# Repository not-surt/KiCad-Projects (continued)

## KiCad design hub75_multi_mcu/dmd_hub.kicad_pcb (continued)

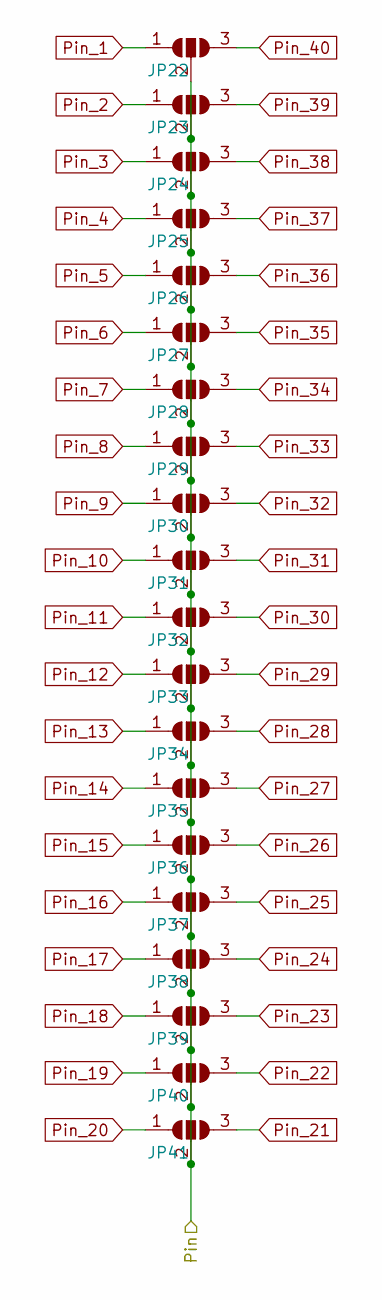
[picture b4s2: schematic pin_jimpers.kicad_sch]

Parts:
JP22, JP23, JP24, JP25, JP26, JP27, JP28, JP29, JP30, JP31, JP32, JP33, JP34, JP35, JP36, JP37, JP38, JP39, JP40, JP41: SolderJumper_3_Open; SolderJumper-mini-3

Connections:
Pin_1: JP22.1 (A); also elsewhere on the board
Pin_2: JP23.1 (A); also elsewhere on the board
Pin_3: JP24.1 (A); also elsewhere on the board
Pin_4: JP25.1 (A); also elsewhere on the board
Pin_5: JP26.1 (A); also elsewhere on the board
Pin_6: JP27.1 (A); also elsewhere on the board
Pin_7: JP28.1 (A); also elsewhere on the board
Pin_8: JP29.1 (A); also elsewhere on the board
Pin_9: JP30.1 (A); also elsewhere on the board
Pin_10: JP31.1 (A); also elsewhere on the board
Pin_11: JP32.1 (A); also elsewhere on the board
Pin_12: JP33.1 (A); also elsewhere on the board
Pin_13: JP34.1 (A); also elsewhere on the board
Pin_14: JP35.1 (A); also elsewhere on the board
Pin_15: JP36.1 (A); also elsewhere on the board
Pin_16: JP37.1 (A); also elsewhere on the board
Pin_17: JP38.1 (A); also elsewhere on the board
Pin_18: JP39.1 (A); also elsewhere on the board
Pin_19: JP40.1 (A); also elsewhere on the board
Pin_20: JP41.1 (A); also elsewhere on the board
Pin_21: JP41.3 (B); also elsewhere on the board
Pin_22: JP40.3 (B); also elsewhere on the board
Pin_23: JP39.3 (B); also elsewhere on the board
Pin_24: JP38.3 (B); also elsewhere on the board
Pin_25: JP37.3 (B); also elsewhere on the board
Pin_26: JP36.3 (B); also elsewhere on the board
Pin_27: JP35.3 (B); also elsewhere on the board
Pin_28: JP34.3 (B); also elsewhere on the board
Pin_29: JP33.3 (B); also elsewhere on the board
Pin_30: JP32.3 (B); also elsewhere on the board
Pin_31: JP31.3 (B); also elsewhere on the board
Pin_32: JP30.3 (B); also elsewhere on the board
Pin_33: JP29.3 (B); also elsewhere on the board
Pin_34: JP28.3 (B); also elsewhere on the board
Pin_35: JP27.3 (B); also elsewhere on the board
Pin_36: JP26.3 (B); also elsewhere on the board
Pin_37: JP25.3 (B); also elsewhere on the board
Pin_38: JP24.3 (B); also elsewhere on the board
Pin_39: JP23.3 (B); also elsewhere on the board
Pin_40: JP22.3 (B); also elsewhere on the board
VCC: JP22.2 (C), JP23.2 (C), JP24.2 (C), JP25.2 (C), JP26.2 (C), JP27.2 (C), JP28.2 (C), JP29.2 (C), JP30.2 (C), JP31.2 (C), JP32.2 (C), JP33.2 (C), JP34.2 (C), JP35.2 (C), JP36.2 (C), JP37.2 (C), JP38.2 (C), JP39.2 (C), JP40.2 (C), JP41.2 (C); also elsewhere on the board

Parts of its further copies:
JP2, JP3, JP4, JP5, JP6, JP7, JP8, JP9, JP10, JP11, JP12, JP13, JP14, JP15, JP16, JP17, JP18, JP19, JP20, JP21, JP42, JP43, JP44, JP45, JP46, JP47, JP48, JP49, JP50, JP51, JP52, JP53, JP54, JP55, JP56, JP57, JP58, JP59, JP60, JP61, JP62, JP63, JP64, JP65, JP66, JP67, JP68, JP69, JP70, JP71, JP72, JP73, JP74, JP75, JP76, JP77, JP78, JP79, JP80, JP81, JP82, JP83, JP84, JP85, JP86, JP87, JP88, JP89, JP90, JP91, JP92, JP93, JP94, JP95, JP96, JP97, JP98, JP99, JP100, JP101, JP102, JP103, JP104, JP105, JP106, JP107, JP108, JP109, JP110, JP111, JP112, JP113, JP114, JP115, JP116, JP117, JP118, JP119, JP120, JP121, JP122, JP123, JP124, JP125, JP126, JP127, JP128, JP129, JP130, JP131, JP132, JP133, JP134, JP135, JP136, JP137, JP138, JP139, JP140, JP141, JP142, JP143, JP144, JP145, JP146, JP147, JP148, JP149, JP150, JP151, JP152, JP153, JP154, JP155, JP156, JP157, JP158, JP159, JP160, JP161, JP162, JP163, JP164, JP165, JP166, JP167, JP168, JP169, JP170, JP171, JP172, JP173, JP174, JP175, JP176, JP177, JP178, JP179, JP180, JP181, JP182, JP183, JP184, JP185, JP186, JP187, JP188, JP189, JP190, JP191, JP192, JP193, JP194, JP195, JP196, JP197, JP198, JP199, JP200, JP201, JP202, JP203, JP204, JP205, JP206, JP207, JP208, JP209, JP210, JP211, JP212, JP213, JP214, JP215, JP216, JP217, JP218, JP219, JP220, JP221, JP222, JP223, JP224, JP225, JP226, JP227, JP228, JP229, JP230, JP231, JP232, JP233, JP234, JP235, JP236, JP237, JP238, JP239, JP240, JP241, JP242, JP243, JP244, JP245, JP246, JP247, JP248, JP249, JP250, JP251, JP252, JP253, JP254, JP255, JP256, JP257, JP258, JP259, JP260, JP261, JP262, JP263, JP264, JP265, JP266, JP267, JP268, JP269, JP270, JP271, JP272, JP273, JP274, JP275, JP276, JP277, JP278, JP279, JP280, JP281, JP282, JP283, JP284, JP285, JP286, JP287, JP288, JP289, JP290, JP291, JP292, JP293, JP294, JP295, JP296, JP297, JP298, JP299, JP300, JP301, JP302, JP303, JP304, JP305, JP306, JP307, JP308, JP309, JP310, JP311, JP312, JP313, JP314, JP315, JP316, JP317, JP318, JP319, JP320, JP321: SolderJumper_3_Open; SolderJumper-mini-3

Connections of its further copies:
/IDC01 (R1): JP42.2 (C), JP43.2 (C), JP44.2 (C), JP45.2 (C), JP46.2 (C), JP47.2 (C), JP48.2 (C), JP49.2 (C), JP50.2 (C), JP51.2 (C), JP52.2 (C), JP53.2 (C), JP54.2 (C), JP55.2 (C), JP56.2 (C), JP57.2 (C), JP58.2 (C), JP59.2 (C), JP60.2 (C), JP61.2 (C); also elsewhere on the board
/IDC02 (G1): JP62.2 (C), JP63.2 (C), JP64.2 (C), JP65.2 (C), JP66.2 (C), JP67.2 (C), JP68.2 (C), JP69.2 (C), JP70.2 (C), JP71.2 (C), JP72.2 (C), JP73.2 (C), JP74.2 (C), JP75.2 (C), JP76.2 (C), JP77.2 (C), JP78.2 (C), JP79.2 (C), JP80.2 (C), JP81.2 (C); also elsewhere on the board
/IDC03 (B1): JP82.2 (C), JP83.2 (C), JP84.2 (C), JP85.2 (C), JP86.2 (C), JP87.2 (C), JP88.2 (C), JP89.2 (C), JP90.2 (C), JP91.2 (C), JP92.2 (C), JP93.2 (C), JP94.2 (C), JP95.2 (C), JP96.2 (C), JP97.2 (C), JP98.2 (C), JP99.2 (C), JP100.2 (C), JP101.2 (C); also elsewhere on the board
/IDC05 (R2): JP102.2 (C), JP103.2 (C), JP104.2 (C), JP105.2 (C), JP106.2 (C), JP107.2 (C), JP108.2 (C), JP109.2 (C), JP110.2 (C), JP111.2 (C), JP112.2 (C), JP113.2 (C), JP114.2 (C), JP115.2 (C), JP116.2 (C), JP117.2 (C), JP118.2 (C), JP119.2 (C), JP120.2 (C), JP121.2 (C); also elsewhere on the board
/IDC06 (G2): JP122.2 (C), JP123.2 (C), JP124.2 (C), JP125.2 (C), JP126.2 (C), JP127.2 (C), JP128.2 (C), JP129.2 (C), JP130.2 (C), JP131.2 (C), JP132.2 (C), JP133.2 (C), JP134.2 (C), JP135.2 (C), JP136.2 (C), JP137.2 (C), JP138.2 (C), JP139.2 (C), JP140.2 (C), JP141.2 (C); also elsewhere on the board
/IDC07 (B2): JP142.2 (C), JP143.2 (C), JP144.2 (C), JP145.2 (C), JP146.2 (C), JP147.2 (C), JP148.2 (C), JP149.2 (C), JP150.2 (C), JP151.2 (C), JP152.2 (C), JP153.2 (C), JP154.2 (C), JP155.2 (C), JP156.2 (C), JP157.2 (C), JP158.2 (C), JP159.2 (C), JP160.2 (C), JP161.2 (C); also elsewhere on the board
/IDC08 (E): JP162.2 (C), JP163.2 (C), JP164.2 (C), JP165.2 (C), JP166.2 (C), JP167.2 (C), JP168.2 (C), JP169.2 (C), JP170.2 (C), JP171.2 (C), JP172.2 (C), JP173.2 (C), JP174.2 (C), JP175.2 (C), JP176.2 (C), JP177.2 (C), JP178.2 (C), JP179.2 (C), JP180.2 (C), JP181.2 (C); also elsewhere on the board
/IDC09 (A): JP182.2 (C), JP183.2 (C), JP184.2 (C), JP185.2 (C), JP186.2 (C), JP187.2 (C), JP188.2 (C), JP189.2 (C), JP190.2 (C), JP191.2 (C), JP192.2 (C), JP193.2 (C), JP194.2 (C), JP195.2 (C), JP196.2 (C), JP197.2 (C), JP198.2 (C), JP199.2 (C), JP200.2 (C), JP201.2 (C); also elsewhere on the board
/IDC10 (B): JP202.2 (C), JP203.2 (C), JP204.2 (C), JP205.2 (C), JP206.2 (C), JP207.2 (C), JP208.2 (C), JP209.2 (C), JP210.2 (C), JP211.2 (C), JP212.2 (C), JP213.2 (C), JP214.2 (C), JP215.2 (C), JP216.2 (C), JP217.2 (C), JP218.2 (C), JP219.2 (C), JP220.2 (C), JP221.2 (C); also elsewhere on the board
/IDC11 (C): JP222.2 (C), JP223.2 (C), JP224.2 (C), JP225.2 (C), JP226.2 (C), JP227.2 (C), JP228.2 (C), JP229.2 (C), JP230.2 (C), JP231.2 (C), JP232.2 (C), JP233.2 (C), JP234.2 (C), JP235.2 (C), JP236.2 (C), JP237.2 (C), JP238.2 (C), JP239.2 (C), JP240.2 (C), JP241.2 (C); also elsewhere on the board
/IDC12 (D): JP242.2 (C), JP243.2 (C), JP244.2 (C), JP245.2 (C), JP246.2 (C), JP247.2 (C), JP248.2 (C), JP249.2 (C), JP250.2 (C), JP251.2 (C), JP252.2 (C), JP253.2 (C), JP254.2 (C), JP255.2 (C), JP256.2 (C), JP257.2 (C), JP258.2 (C), JP259.2 (C), JP260.2 (C), JP261.2 (C); also elsewhere on the board
/IDC13 (CLK): JP262.2 (C), JP263.2 (C), JP264.2 (C), JP265.2 (C), JP266.2 (C), JP267.2 (C), JP268.2 (C), JP269.2 (C), JP270.2 (C), JP271.2 (C), JP272.2 (C), JP273.2 (C), JP274.2 (C), JP275.2 (C), JP276.2 (C), JP277.2 (C), JP278.2 (C), JP279.2 (C), JP280.2 (C), JP281.2 (C); also elsewhere on the board
/IDC14 (LAT): JP282.2 (C), JP283.2 (C), JP284.2 (C), JP285.2 (C), JP286.2 (C), JP287.2 (C), JP288.2 (C), JP289.2 (C), JP290.2 (C), JP291.2 (C), JP292.2 (C), JP293.2 (C), JP294.2 (C), JP295.2 (C), JP296.2 (C), JP297.2 (C), JP298.2 (C), JP299.2 (C), JP300.2 (C), JP301.2 (C); also elsewhere on the board
/IDC15 (OE): JP302.2 (C), JP303.2 (C), JP304.2 (C), JP305.2 (C), JP306.2 (C), JP307.2 (C), JP308.2 (C), JP309.2 (C), JP310.2 (C), JP311.2 (C), JP312.2 (C), JP313.2 (C), JP314.2 (C), JP315.2 (C), JP316.2 (C), JP317.2 (C), JP318.2 (C), JP319.2 (C), JP320.2 (C), JP321.2 (C); also elsewhere on the board
GND: JP2.2 (C), JP3.2 (C), JP4.2 (C), JP5.2 (C), JP6.2 (C), JP7.2 (C), JP8.2 (C), JP9.2 (C), JP10.2 (C), JP11.2 (C), JP12.2 (C), JP13.2 (C), JP14.2 (C), JP15.2 (C), JP16.2 (C), JP17.2 (C), JP18.2 (C), JP19.2 (C), JP20.2 (C), JP21.2 (C); also elsewhere on the board
Pin_1: JP2.1 (A), JP42.1 (A), JP62.1 (A), JP82.1 (A), JP102.1 (A), JP122.1 (A), JP142.1 (A), JP162.1 (A), JP182.1 (A), JP202.1 (A), JP222.1 (A), JP242.1 (A), JP262.1 (A), JP282.1 (A), JP302.1 (A); also elsewhere on the board
Pin_2: JP3.1 (A), JP43.1 (A), JP63.1 (A), JP83.1 (A), JP103.1 (A), JP123.1 (A), JP143.1 (A), JP163.1 (A), JP183.1 (A), JP203.1 (A), JP223.1 (A), JP243.1 (A), JP263.1 (A), JP283.1 (A), JP303.1 (A); also elsewhere on the board
Pin_3: JP4.1 (A), JP44.1 (A), JP64.1 (A), JP84.1 (A), JP104.1 (A), JP124.1 (A), JP144.1 (A), JP164.1 (A), JP184.1 (A), JP204.1 (A), JP224.1 (A), JP244.1 (A), JP264.1 (A), JP284.1 (A), JP304.1 (A); also elsewhere on the board
Pin_4: JP5.1 (A), JP45.1 (A), JP65.1 (A), JP85.1 (A), JP105.1 (A), JP125.1 (A), JP145.1 (A), JP165.1 (A), JP185.1 (A), JP205.1 (A), JP225.1 (A), JP245.1 (A), JP265.1 (A), JP285.1 (A), JP305.1 (A); also elsewhere on the board
Pin_5: JP6.1 (A), JP46.1 (A), JP66.1 (A), JP86.1 (A), JP106.1 (A), JP126.1 (A), JP146.1 (A), JP166.1 (A), JP186.1 (A), JP206.1 (A), JP226.1 (A), JP246.1 (A), JP266.1 (A), JP286.1 (A), JP306.1 (A); also elsewhere on the board
Pin_6: JP7.1 (A), JP47.1 (A), JP67.1 (A), JP87.1 (A), JP107.1 (A), JP127.1 (A), JP147.1 (A), JP167.1 (A), JP187.1 (A), JP207.1 (A), JP227.1 (A), JP247.1 (A), JP267.1 (A), JP287.1 (A), JP307.1 (A); also elsewhere on the board
Pin_7: JP8.1 (A), JP48.1 (A), JP68.1 (A), JP88.1 (A), JP108.1 (A), JP128.1 (A), JP148.1 (A), JP168.1 (A), JP188.1 (A), JP208.1 (A), JP228.1 (A), JP248.1 (A), JP268.1 (A), JP288.1 (A), JP308.1 (A); also elsewhere on the board
Pin_8: JP9.1 (A), JP49.1 (A), JP69.1 (A), JP89.1 (A), JP109.1 (A), JP129.1 (A), JP149.1 (A), JP169.1 (A), JP189.1 (A), JP209.1 (A), JP229.1 (A), JP249.1 (A), JP269.1 (A), JP289.1 (A), JP309.1 (A); also elsewhere on the board
Pin_9: JP10.1 (A), JP50.1 (A), JP70.1 (A), JP90.1 (A), JP110.1 (A), JP130.1 (A), JP150.1 (A), JP170.1 (A), JP190.1 (A), JP210.1 (A), JP230.1 (A), JP250.1 (A), JP270.1 (A), JP290.1 (A), JP310.1 (A); also elsewhere on the board
Pin_10: JP11.1 (A), JP51.1 (A), JP71.1 (A), JP91.1 (A), JP111.1 (A), JP131.1 (A), JP151.1 (A), JP171.1 (A), JP191.1 (A), JP211.1 (A), JP231.1 (A), JP251.1 (A), JP271.1 (A), JP291.1 (A), JP311.1 (A); also elsewhere on the board
Pin_11: JP12.1 (A), JP52.1 (A), JP72.1 (A), JP92.1 (A), JP112.1 (A), JP132.1 (A), JP152.1 (A), JP172.1 (A), JP192.1 (A), JP212.1 (A), JP232.1 (A), JP252.1 (A), JP272.1 (A), JP292.1 (A), JP312.1 (A); also elsewhere on the board
Pin_12: JP13.1 (A), JP53.1 (A), JP73.1 (A), JP93.1 (A), JP113.1 (A), JP133.1 (A), JP153.1 (A), JP173.1 (A), JP193.1 (A), JP213.1 (A), JP233.1 (A), JP253.1 (A), JP273.1 (A), JP293.1 (A), JP313.1 (A); also elsewhere on the board
Pin_13: JP14.1 (A), JP54.1 (A), JP74.1 (A), JP94.1 (A), JP114.1 (A), JP134.1 (A), JP154.1 (A), JP174.1 (A), JP194.1 (A), JP214.1 (A), JP234.1 (A), JP254.1 (A), JP274.1 (A), JP294.1 (A), JP314.1 (A); also elsewhere on the board
Pin_14: JP15.1 (A), JP55.1 (A), JP75.1 (A), JP95.1 (A), JP115.1 (A), JP135.1 (A), JP155.1 (A), JP175.1 (A), JP195.1 (A), JP215.1 (A), JP235.1 (A), JP255.1 (A), JP275.1 (A), JP295.1 (A), JP315.1 (A); also elsewhere on the board
Pin_15: JP16.1 (A), JP56.1 (A), JP76.1 (A), JP96.1 (A), JP116.1 (A), JP136.1 (A), JP156.1 (A), JP176.1 (A), JP196.1 (A), JP216.1 (A), JP236.1 (A), JP256.1 (A), JP276.1 (A), JP296.1 (A), JP316.1 (A); also elsewhere on the board
Pin_16: JP17.1 (A), JP57.1 (A), JP77.1 (A), JP97.1 (A), JP117.1 (A), JP137.1 (A), JP157.1 (A), JP177.1 (A), JP197.1 (A), JP217.1 (A), JP237.1 (A), JP257.1 (A), JP277.1 (A), JP297.1 (A), JP317.1 (A); also elsewhere on the board
Pin_17: JP18.1 (A), JP58.1 (A), JP78.1 (A), JP98.1 (A), JP118.1 (A), JP138.1 (A), JP158.1 (A), JP178.1 (A), JP198.1 (A), JP218.1 (A), JP238.1 (A), JP258.1 (A), JP278.1 (A), JP298.1 (A), JP318.1 (A); also elsewhere on the board
Pin_18: JP19.1 (A), JP59.1 (A), JP79.1 (A), JP99.1 (A), JP119.1 (A), JP139.1 (A), JP159.1 (A), JP179.1 (A), JP199.1 (A), JP219.1 (A), JP239.1 (A), JP259.1 (A), JP279.1 (A), JP299.1 (A), JP319.1 (A); also elsewhere on the board
Pin_19: JP20.1 (A), JP60.1 (A), JP80.1 (A), JP100.1 (A), JP120.1 (A), JP140.1 (A), JP160.1 (A), JP180.1 (A), JP200.1 (A), JP220.1 (A), JP240.1 (A), JP260.1 (A), JP280.1 (A), JP300.1 (A), JP320.1 (A); also elsewhere on the board
Pin_20: JP21.1 (A), JP61.1 (A), JP81.1 (A), JP101.1 (A), JP121.1 (A), JP141.1 (A), JP161.1 (A), JP181.1 (A), JP201.1 (A), JP221.1 (A), JP241.1 (A), JP261.1 (A), JP281.1 (A), JP301.1 (A), JP321.1 (A); also elsewhere on the board
Pin_21: JP21.3 (B), JP61.3 (B), JP81.3 (B), JP101.3 (B), JP121.3 (B), JP141.3 (B), JP161.3 (B), JP181.3 (B), JP201.3 (B), JP221.3 (B), JP241.3 (B), JP261.3 (B), JP281.3 (B), JP301.3 (B), JP321.3 (B); also elsewhere on the board
Pin_22: JP20.3 (B), JP60.3 (B), JP80.3 (B), JP100.3 (B), JP120.3 (B), JP140.3 (B), JP160.3 (B), JP180.3 (B), JP200.3 (B), JP220.3 (B), JP240.3 (B), JP260.3 (B), JP280.3 (B), JP300.3 (B), JP320.3 (B); also elsewhere on the board
Pin_23: JP19.3 (B), JP59.3 (B), JP79.3 (B), JP99.3 (B), JP119.3 (B), JP139.3 (B), JP159.3 (B), JP179.3 (B), JP199.3 (B), JP219.3 (B), JP239.3 (B), JP259.3 (B), JP279.3 (B), JP299.3 (B), JP319.3 (B); also elsewhere on the board
Pin_24: JP18.3 (B), JP58.3 (B), JP78.3 (B), JP98.3 (B), JP118.3 (B), JP138.3 (B), JP158.3 (B), JP178.3 (B), JP198.3 (B), JP218.3 (B), JP238.3 (B), JP258.3 (B), JP278.3 (B), JP298.3 (B), JP318.3 (B); also elsewhere on the board
Pin_25: JP17.3 (B), JP57.3 (B), JP77.3 (B), JP97.3 (B), JP117.3 (B), JP137.3 (B), JP157.3 (B), JP177.3 (B), JP197.3 (B), JP217.3 (B), JP237.3 (B), JP257.3 (B), JP277.3 (B), JP297.3 (B), JP317.3 (B); also elsewhere on the board
Pin_26: JP16.3 (B), JP56.3 (B), JP76.3 (B), JP96.3 (B), JP116.3 (B), JP136.3 (B), JP156.3 (B), JP176.3 (B), JP196.3 (B), JP216.3 (B), JP236.3 (B), JP256.3 (B), JP276.3 (B), JP296.3 (B), JP316.3 (B); also elsewhere on the board
Pin_27: JP15.3 (B), JP55.3 (B), JP75.3 (B), JP95.3 (B), JP115.3 (B), JP135.3 (B), JP155.3 (B), JP175.3 (B), JP195.3 (B), JP215.3 (B), JP235.3 (B), JP255.3 (B), JP275.3 (B), JP295.3 (B), JP315.3 (B); also elsewhere on the board
Pin_28: JP14.3 (B), JP54.3 (B), JP74.3 (B), JP94.3 (B), JP114.3 (B), JP134.3 (B), JP154.3 (B), JP174.3 (B), JP194.3 (B), JP214.3 (B), JP234.3 (B), JP254.3 (B), JP274.3 (B), JP294.3 (B), JP314.3 (B); also elsewhere on the board
Pin_29: JP13.3 (B), JP53.3 (B), JP73.3 (B), JP93.3 (B), JP113.3 (B), JP133.3 (B), JP153.3 (B), JP173.3 (B), JP193.3 (B), JP213.3 (B), JP233.3 (B), JP253.3 (B), JP273.3 (B), JP293.3 (B), JP313.3 (B); also elsewhere on the board
Pin_30: JP12.3 (B), JP52.3 (B), JP72.3 (B), JP92.3 (B), JP112.3 (B), JP132.3 (B), JP152.3 (B), JP172.3 (B), JP192.3 (B), JP212.3 (B), JP232.3 (B), JP252.3 (B), JP272.3 (B), JP292.3 (B), JP312.3 (B); also elsewhere on the board
Pin_31: JP11.3 (B), JP51.3 (B), JP71.3 (B), JP91.3 (B), JP111.3 (B), JP131.3 (B), JP151.3 (B), JP171.3 (B), JP191.3 (B), JP211.3 (B), JP231.3 (B), JP251.3 (B), JP271.3 (B), JP291.3 (B), JP311.3 (B); also elsewhere on the board
Pin_32: JP10.3 (B), JP50.3 (B), JP70.3 (B), JP90.3 (B), JP110.3 (B), JP130.3 (B), JP150.3 (B), JP170.3 (B), JP190.3 (B), JP210.3 (B), JP230.3 (B), JP250.3 (B), JP270.3 (B), JP290.3 (B), JP310.3 (B); also elsewhere on the board
Pin_33: JP9.3 (B), JP49.3 (B), JP69.3 (B), JP89.3 (B), JP109.3 (B), JP129.3 (B), JP149.3 (B), JP169.3 (B), JP189.3 (B), JP209.3 (B), JP229.3 (B), JP249.3 (B), JP269.3 (B), JP289.3 (B), JP309.3 (B); also elsewhere on the board
Pin_34: JP8.3 (B), JP48.3 (B), JP68.3 (B), JP88.3 (B), JP108.3 (B), JP128.3 (B), JP148.3 (B), JP168.3 (B), JP188.3 (B), JP208.3 (B), JP228.3 (B), JP248.3 (B), JP268.3 (B), JP288.3 (B), JP308.3 (B); also elsewhere on the board
Pin_35: JP7.3 (B), JP47.3 (B), JP67.3 (B), JP87.3 (B), JP107.3 (B), JP127.3 (B), JP147.3 (B), JP167.3 (B), JP187.3 (B), JP207.3 (B), JP227.3 (B), JP247.3 (B), JP267.3 (B), JP287.3 (B), JP307.3 (B); also elsewhere on the board
Pin_36: JP6.3 (B), JP46.3 (B), JP66.3 (B), JP86.3 (B), JP106.3 (B), JP126.3 (B), JP146.3 (B), JP166.3 (B), JP186.3 (B), JP206.3 (B), JP226.3 (B), JP246.3 (B), JP266.3 (B), JP286.3 (B), JP306.3 (B); also elsewhere on the board
Pin_37: JP5.3 (B), JP45.3 (B), JP65.3 (B), JP85.3 (B), JP105.3 (B), JP125.3 (B), JP145.3 (B), JP165.3 (B), JP185.3 (B), JP205.3 (B), JP225.3 (B), JP245.3 (B), JP265.3 (B), JP285.3 (B), JP305.3 (B); also elsewhere on the board
Pin_38: JP4.3 (B), JP44.3 (B), JP64.3 (B), JP84.3 (B), JP104.3 (B), JP124.3 (B), JP144.3 (B), JP164.3 (B), JP184.3 (B), JP204.3 (B), JP224.3 (B), JP244.3 (B), JP264.3 (B), JP284.3 (B), JP304.3 (B); also elsewhere on the board
Pin_39: JP3.3 (B), JP43.3 (B), JP63.3 (B), JP83.3 (B), JP103.3 (B), JP123.3 (B), JP143.3 (B), JP163.3 (B), JP183.3 (B), JP203.3 (B), JP223.3 (B), JP243.3 (B), JP263.3 (B), JP283.3 (B), JP303.3 (B); also elsewhere on the board
Pin_40: JP2.3 (B), JP42.3 (B), JP62.3 (B), JP82.3 (B), JP102.3 (B), JP122.3 (B), JP142.3 (B), JP162.3 (B), JP182.3 (B), JP202.3 (B), JP222.3 (B), JP242.3 (B), JP262.3 (B), JP282.3 (B), JP302.3 (B); also elsewhere on the board

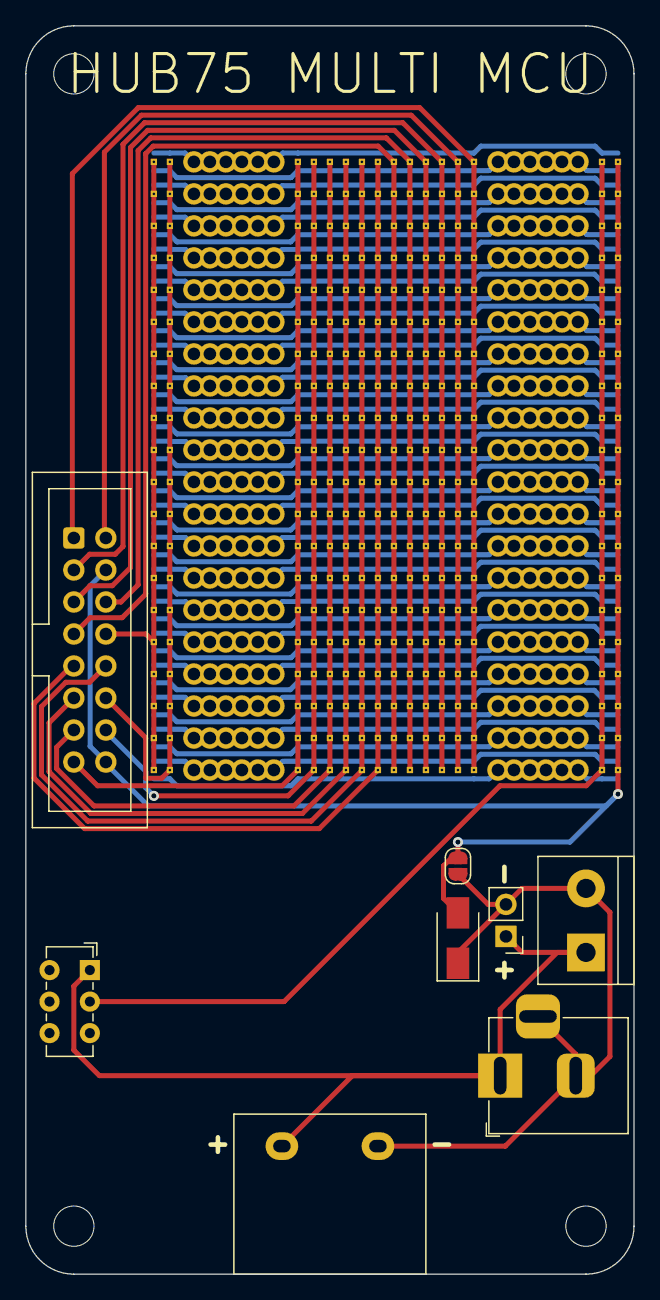
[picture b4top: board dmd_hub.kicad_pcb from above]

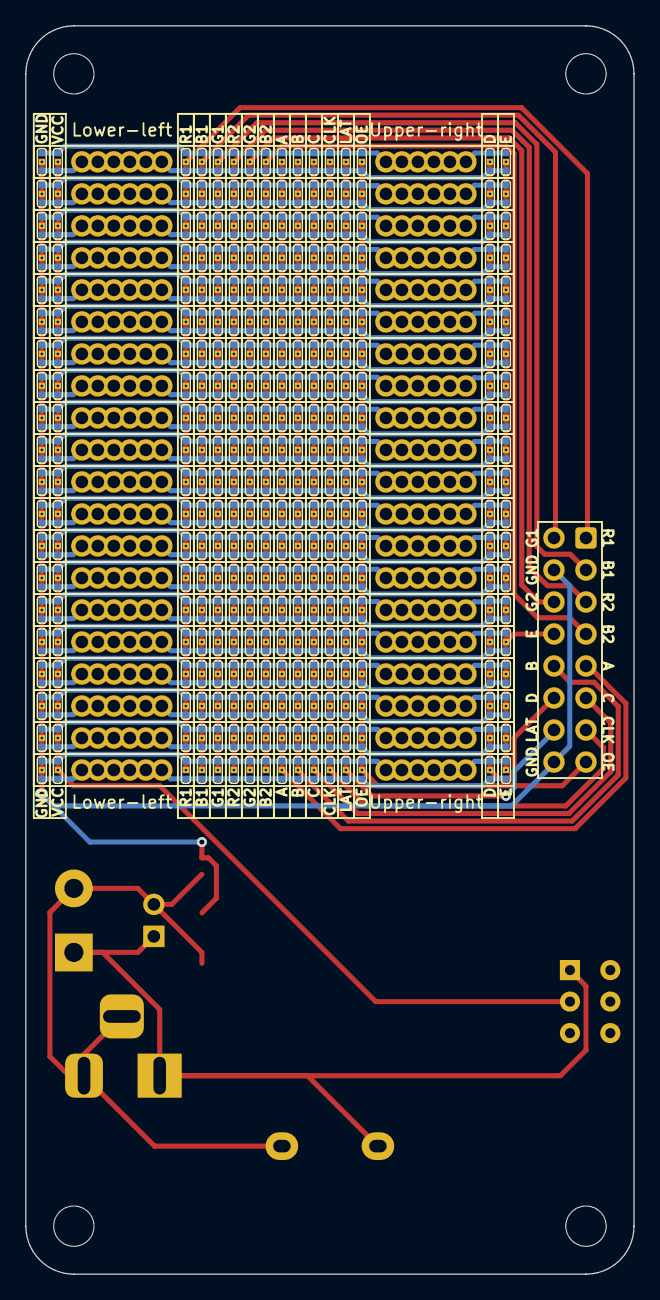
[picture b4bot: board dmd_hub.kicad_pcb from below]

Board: 2 copper layers, 48.3 x 99.1 mm, 340 parts (320 on the bottom side), 58 nets.
